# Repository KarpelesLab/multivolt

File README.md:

# MultiVolt — breadboard power & level-translation boards

Two KiCad 10 boards, designed for JLCPCB assembly:

| Board | What it is | Size | Parts cost* |
|---|---|---|---|
| **MultiVolt PSU** (`boards/mvpsu`) | USB-C PD supply that plugs into both breadboard power-rail pairs. Each side gets its own voltage, picked with a jumper: **1.2 / 1.5 / 1.8 / 2.5 / 3.3 / 5.0 V**. Latching overcurrent protection with LEDs. | 60 × 57 mm | ≈ $6.9 |
| **MultiVolt LVL4** (`boards/lvl4`) | 4-channel fixed-direction level translator, DIP-20 footprint (straddles the centre channel). | 12.7 × 30 mm | ≈ $1.35 |

\*Parts only, JLCPCB prices at qty 50/100, October 2026. Extended-part setup fees, PCB and assembly cost come on top.

### Repository layout
```
designs/       board descriptions (Python) - edit these, not the KiCad files
  psu.py         MultiVolt PSU
  iomodule.py    MultiVolt LVL4
lib/           custom KiCad symbol (INA301)
tools/         generator: schematic writer, PCB builder, autoroute, JLC export, BOM checker
boards/<name>/ generated KiCad 10 project (.kicad_sch/.kicad_pcb/.kicad_pro)
  fab/           gerbers zip, JLC BOM + CPL, schematic PDF, 3D renders
```

---

## MultiVolt PSU

### How it works
* **Input:** USB-C. A **CH224A** asks the charger for **9 V** over USB PD. If the charger can't do PD, the board still runs from 5 V, but the 5 V setting then gives about 4.8 V.
* **Two rails (L / R), each a TPS62933P synchronous buck** (3 A part, 500 kHz). Usable output is **up to 2 A per rail**, set by the protection.
* **Voltage select:** a 2×6 header per rail. Each row is one voltage; put a single jumper across the row you want.
  * **No jumper = rail off (≈0 V).** The FB pin is pulled to 3.3 V through 1 MΩ, so the converter just idles.
  * Two jumpers by mistake: the output lands *between* the two choices, never above the higher one.
  * Computed outputs: 1.202 / 1.500 / 1.800 / 2.501 / 3.296 / 4.992 V nominal, within about ±2 % worst case (see `tools/fb_string.py`).
  * Feedback is taken *after* the current shunt, so the shunt's voltage drop doesn't lower the output.
* **Protection:** an **INA301** watches a 50 mΩ shunt on each rail. Over the limit, it latches, pulls the buck's EN low and lights the **red OC LED**.
  * **ILIM jumper fitted = 1 A trip, removed = 2 A.**
  * Press **RESET** to re-arm both rails.
  * A ~94 µs filter stops normal capacitor inrush from tripping it. Short-circuit current is still limited cycle by cycle inside the TPS62933.
* **LEDs:**
  * **PD** (yellow): the PD contract was negotiated.
  * **OK** (yellow-green, one per rail): the converter reports power-good.
  * **OC** (red, one per rail): overcurrent latched.
* **Outputs:** the rail pins plug into both breadboard power-rail pairs (GND, + on each side). There's also a 4-pin **AUX** header (L+, G, G, R+) for wiring off-board.
* A 1 kΩ bleeder on each rail drops the old voltage in about 35 ms after you switch to a lower setting. The buck can't pull its output down by itself.

### Breadboard rail pins
Sized for MB102-style 830-point breadboards, 55–56 mm wide.

* **Positions:** the inner rail holes are 0.825″ (20.955 mm) from the centreline and the outer ones 0.925″ (23.495 mm). The rail pairs are half a pitch off the 0.1″ grid of the main area.
* **Pins:** each side has **two 2-pin headers in holes 1 and 5 of a rail group (10.16 mm apart)**, so the board sits firmly. Rail holes come in groups of five with a blank position between groups.
* **Polarity:** the order is **GND, +** on both sides, reading left to right with the USB connector facing away from the breadboard. To flip it to + then GND, set `RAIL_ORDER = "+G"` in `designs/psu.py` and regenerate.
* **Mounting:** the headers go on the **bottom** side, pins pointing down.

### Usage notes
* Choose the voltage **before** connecting sensitive parts. Changing the jumper on a live, loaded rail can trip OC: press RESET.
* The OK LED stays off with no jumper. That's expected.
* Inrush: about 46 µF across VBUS. PD chargers are fine with this, but it's above the old USB 2.0 limit of 10 µF.

---

## MultiVolt LVL4 (level translator)

Four **SN74LXC1T45** channels. Each side runs from its own supply, **1.1–5.5 V**, up to 420 Mbps. There's **no automatic direction sensing**: each channel's direction is set by its DIR pin.

* **Input threshold** follows the supply of the *input* side. The **output** swings to the supply of the *output* side.
* **DIRn high or unconnected** (100 k pull-up to VA) = **A → B**. **DIRn tied to GND** = **B → A**. DIR is referenced to **VA**.
* Push-pull only. **Not suitable for I²C or other open-drain buses.**

```
          ┌──────── LVL4 ────────┐
   VA   1 │●                     │ 1  VB
   A1   2 │                      │ 2  B1
   DIR1 3 │                      │ 3  GND
   A2   4 │                      │ 4  B2
   DIR2 5 │                      │ 5  GND
   A3   6 │                      │ 6  B3
   DIR3 7 │                      │ 7  GND
   A4   8 │                      │ 8  B4
   DIR4 9 │                      │ 9  GND
   GND 10 │                      │ 10 GND
          └──────────────────────┘   rows 0.3" apart (DIP-20)
```
Typical setup: VA and VB come from the two PSU rails, for example the L rail at 1.8 V and the R rail at 3.3 V.

---

## Ordering at JLCPCB
Upload these files from `boards/<name>/fab/`:
* `<name>_gerbers.zip`
* `<name>_bom_jlc.csv`
* `<name>_cpl_jlc.csv`

Board settings: 2 layers, 1.6 mm, any finish.

* **Check part rotations in JLC's placement preview before paying.** KiCad and LCSC sometimes disagree on which way a package faces. Rotation fixes go in `ROT_FIX` in `tools/jlc_files.py`. Connectors whose KiCad origin isn't the part centre (pin headers, USB-C) are placed on their pad centre (`PAD_CENTER`).
* The pin headers are through-hole parts. Use JLC's THT assembly option or solder them yourself. On both boards the breadboard headers mount on the **bottom** side.
* Jumper shunts aren't in the BOM: 2 to 4 per PSU (one per VSEL header, plus one per ILIM header if you want the 1 A trip). Standard 2.54 mm shunts, e.g. LCSC C100114.
* Rules used: 0.15 mm clearance, 0.10 mm minimum trace (only at fine-pitch pads), 0.3 mm vias. All within JLC's standard 2-layer process.

## Regenerating
Everything is generated from Python. Edit `designs/*.py`, then run:
```sh
tools/make_board.sh designs/psu.py mvpsu --passes 40      # schematic, ERC, netlist check, PCB, autoroute, DRC
tools/make_board.sh designs/iomodule.py lvl4 --passes 25
tools/fab.sh mvpsu && tools/fab.sh lvl4                     # gerbers, BOM, CPL, PDF, renders
python3 tools/check_bom.py boards/mvpsu/mvpsu.design.json 50   # live JLC stock/price check
```
Requires KiCad 10 (macOS paths in the scripts). Run `tools/setup.sh` once to download Freerouting 2.5 and a Java 25 runtime into `tools/bin/` (not committed).

The switching-regulator power paths, VBUS distribution and rail outputs are hand-placed in the design files. Freerouting routes the remaining signals.

## Before a production run
These boards haven't been built yet. On the first prototypes:
1. Check each tap's output voltage with no load and with a 1 A load.
2. Run a load step on the 1.2 V and 5 V taps to check for ringing. This is the TPS62933 loop with 4.7 µH and 3×22 µF across the whole 1.2–5 V range.
3. Confirm the OC trip point and RESET behaviour.
4. Check how hot the converters get at 2 A.

## License
Copyright 2026 Karpeles Lab Inc.

This hardware design, including the generator scripts that produce it, is licensed under the **CERN Open Hardware Licence Version 2 – Strongly Reciprocal** (CERN-OHL-S v2). See [`LICENSE`](LICENSE).

You may build, modify, sell and distribute boards made from this design. If you distribute boards or modified designs, you must keep the copyright and licence notices and make your complete modified source available under the same licence.

Source location: <https://github.com/KarpelesLab/multivolt>

This source is distributed WITHOUT ANY EXPRESS OR IMPLIED WARRANTY, INCLUDING OF MERCHANTABILITY, SATISFACTORY QUALITY AND FITNESS FOR A PARTICULAR PURPOSE. Please see the CERN-OHL-S v2 for applicable conditions.

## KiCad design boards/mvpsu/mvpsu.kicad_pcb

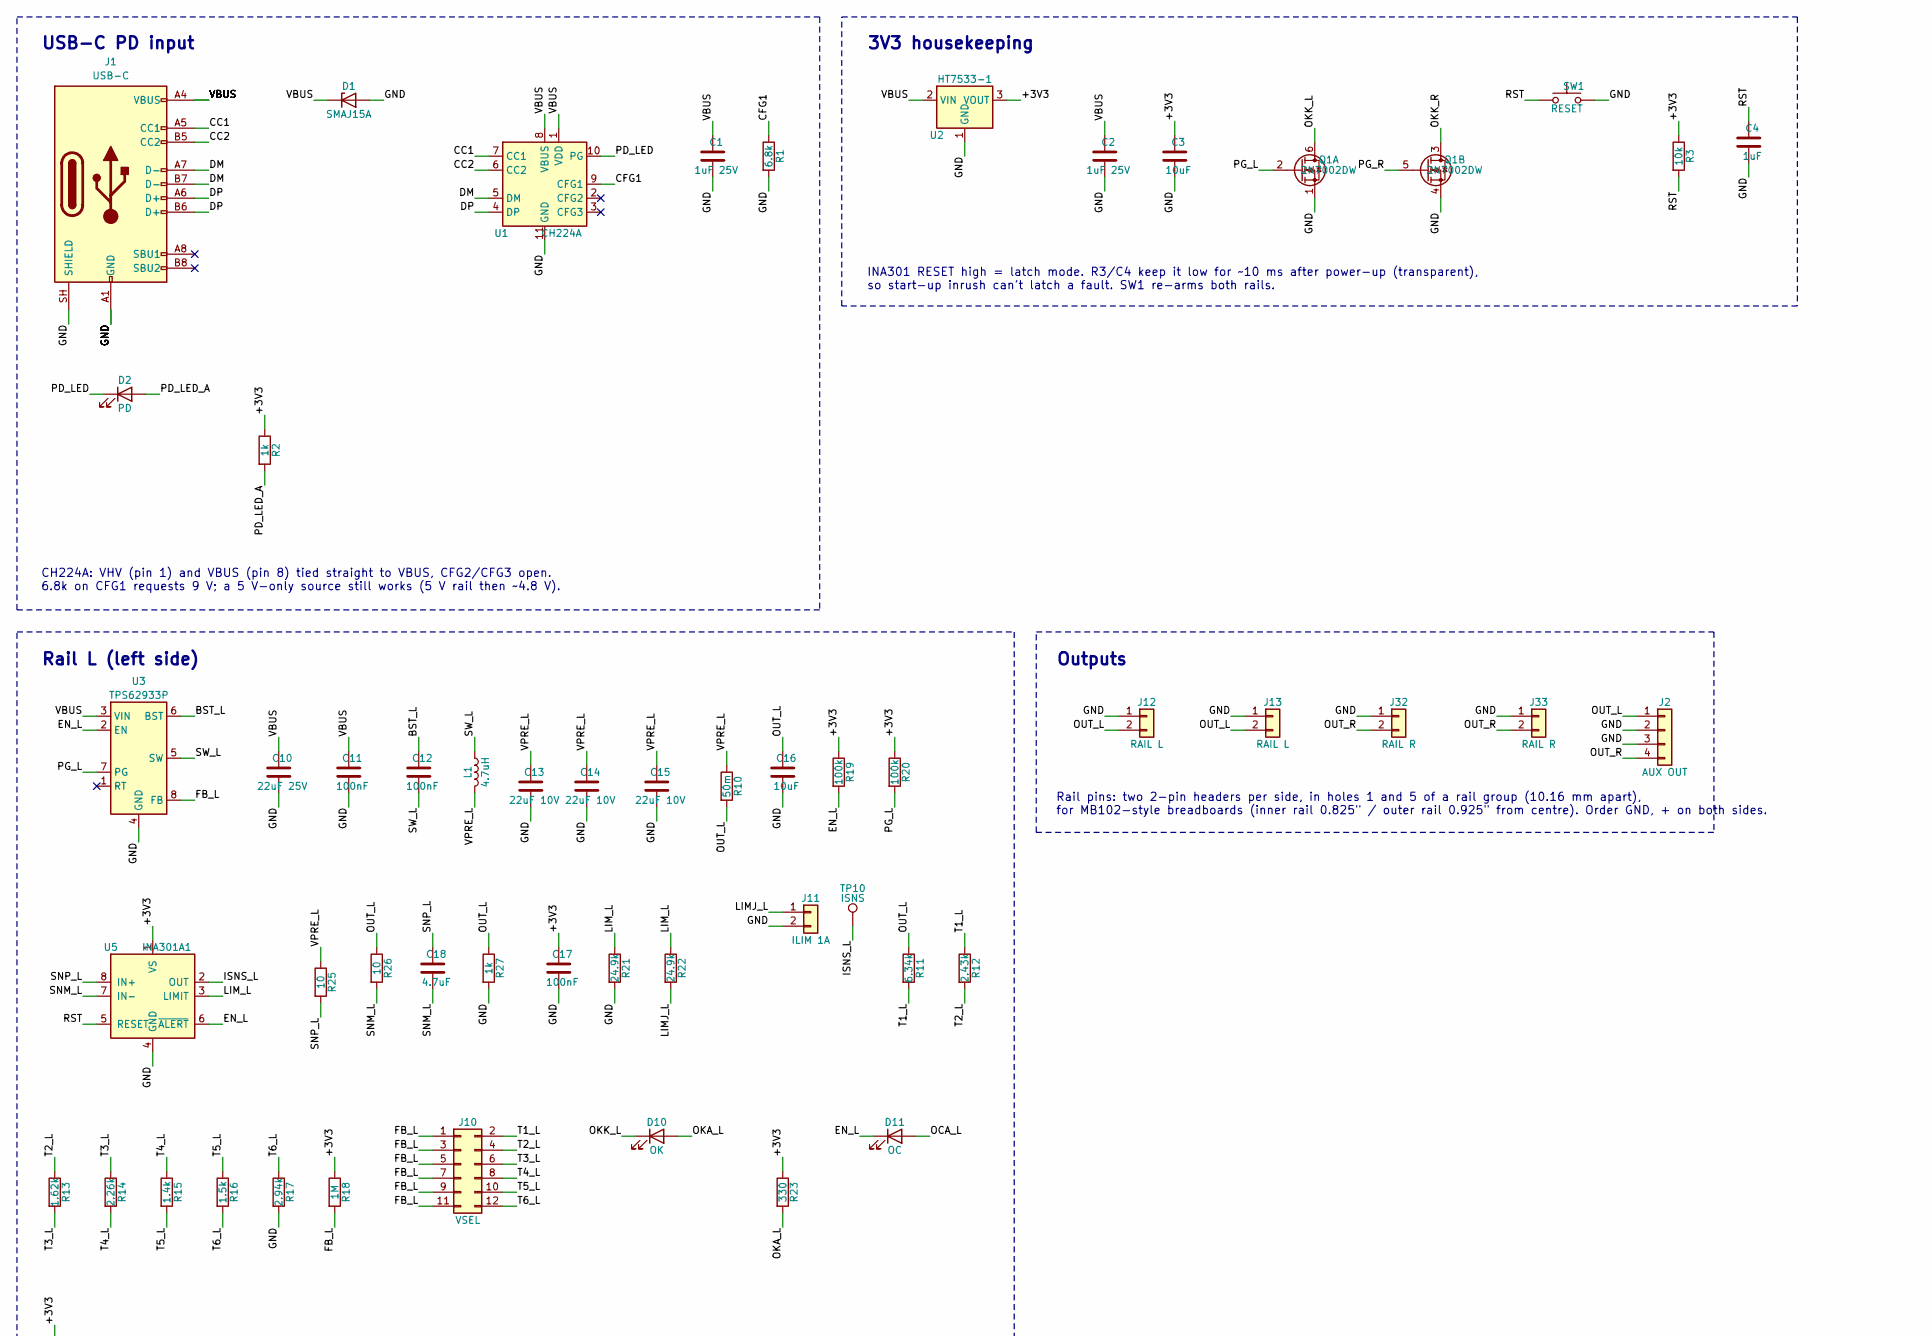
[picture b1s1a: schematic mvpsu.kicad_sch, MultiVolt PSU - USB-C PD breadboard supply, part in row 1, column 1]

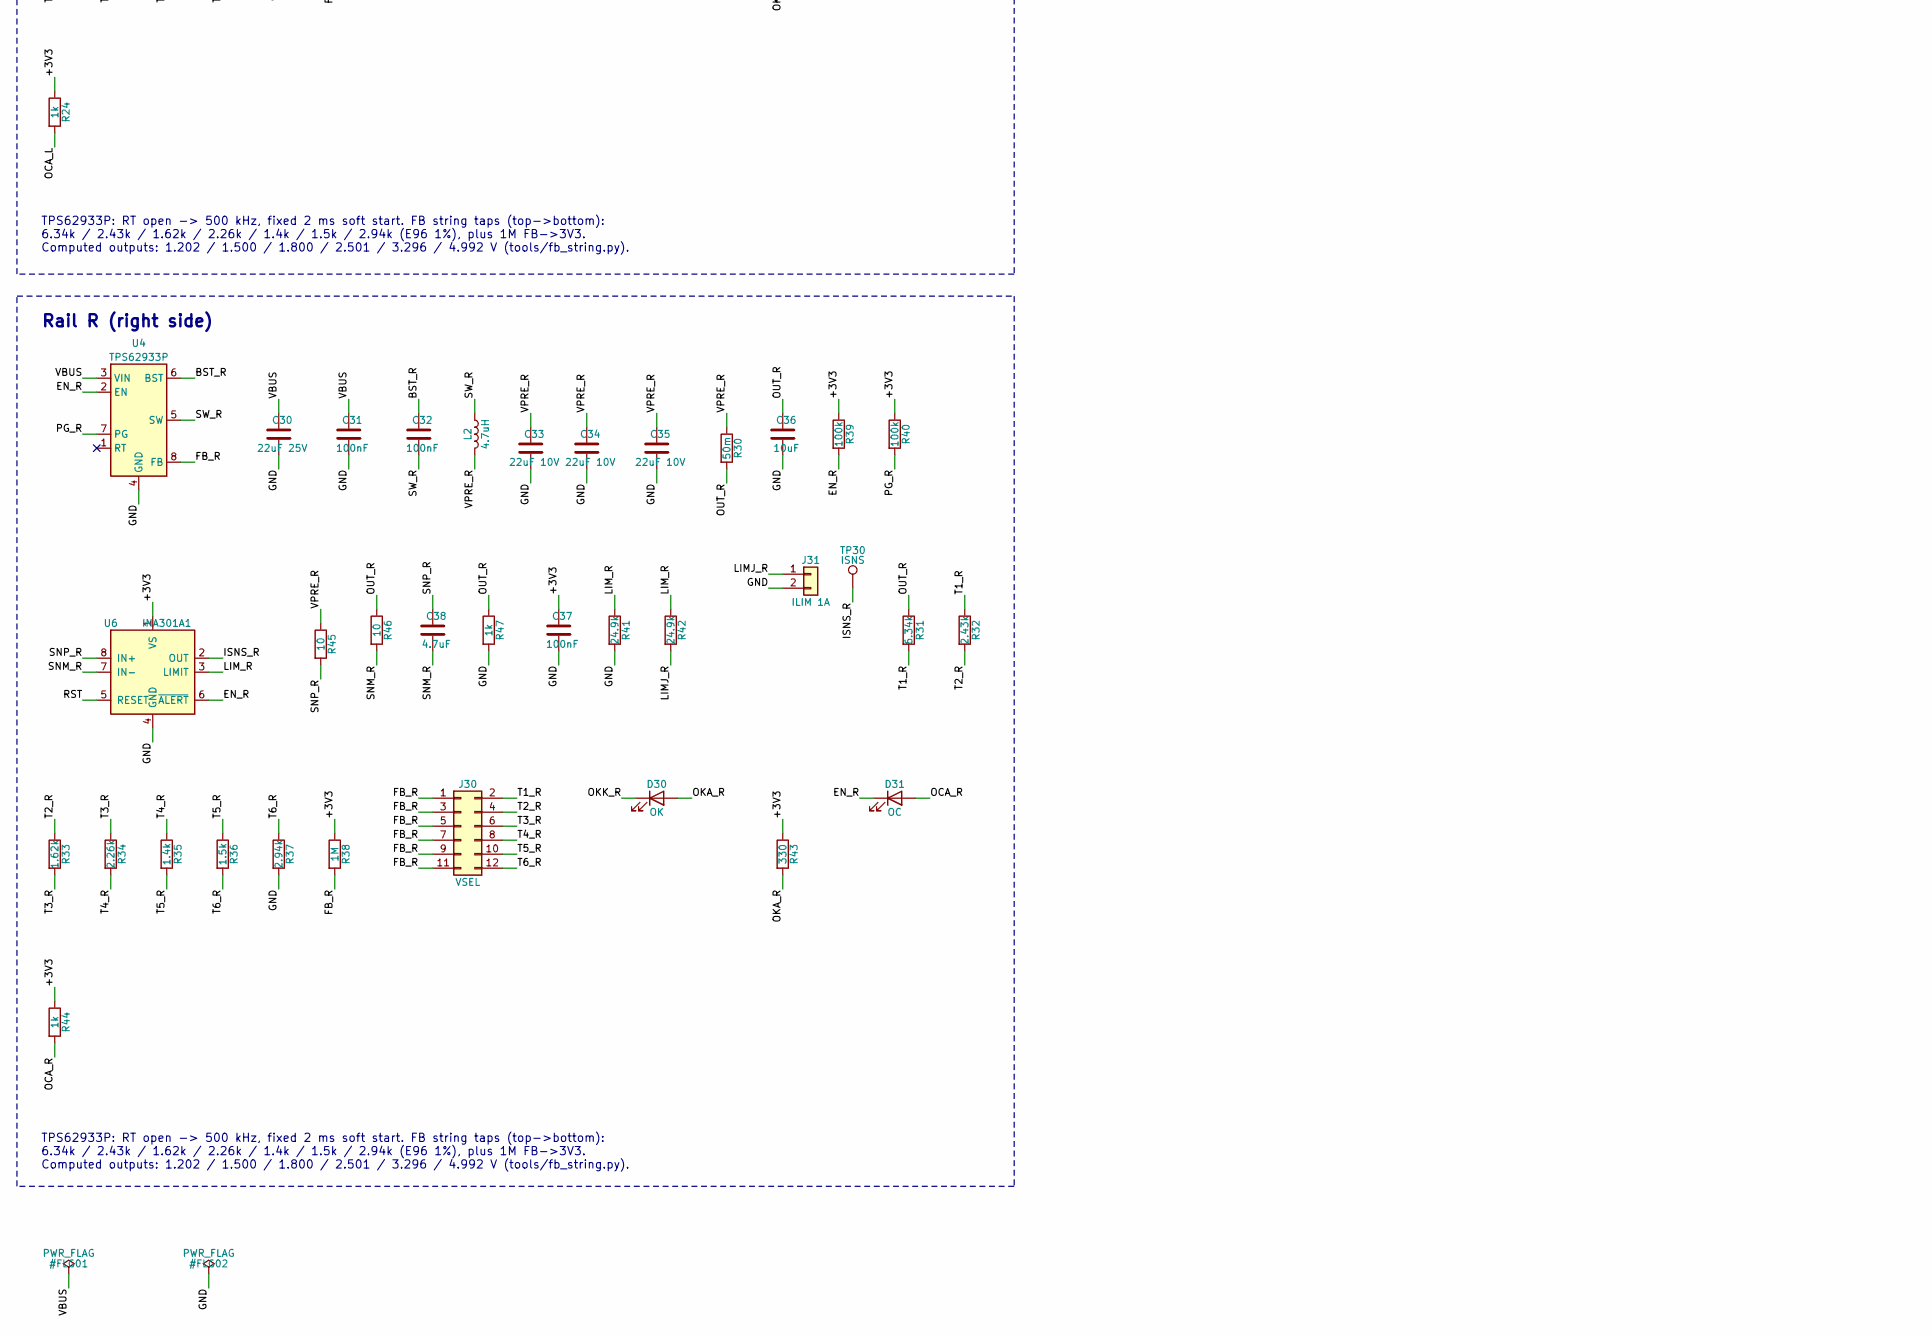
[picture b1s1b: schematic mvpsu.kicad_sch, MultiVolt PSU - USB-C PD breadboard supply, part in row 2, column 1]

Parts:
C1, C2: 1uF 25V; C_0402_1005Metric; LCSC C52923
C3, C16, C36: 10uF; C_0603_1608Metric; LCSC C19702
C4: 1uF; C_0402_1005Metric; LCSC C52923
C10, C30: 22uF 25V; C_1206_3216Metric; LCSC C12891
C11, C12, C17, C31, C32, C37: 100nF; C_0402_1005Metric; LCSC C1525
C13, C14, C15, C33, C34, C35: 22uF 10V; C_0805_2012Metric; LCSC C29277
C18, C38: 4.7uF; C_0402_1005Metric; LCSC C106859
D1: SMAJ15A; D_SMA; LCSC C86819
D2: PD; LED_0603_1608Metric; MPN KT-0603Y; LCSC C2287
D10, D30: OK; LED_0603_1608Metric; MPN KT-0603YG; LCSC C2289
D11, D31: OC; LED_0603_1608Metric; MPN KT-0603R; LCSC C2286
J1: USB-C; USB_C_Receptacle_HRO_TYPE-C-31-M-12; MPN TYPE-C-31-M-12; LCSC C165948
J2: AUX OUT; PinHeader_1x04_P2.54mm_Vertical; LCSC C2691448
J10, J30: VSEL; PinHeader_2x06_P2.54mm_Vertical; LCSC C492423
J11, J31: ILIM 1A; PinHeader_1x02_P2.54mm_Vertical; LCSC C492401
J12, J13: RAIL L; PinHeader_1x02_P2.54mm_Vertical; LCSC C492401
J32, J33: RAIL R; PinHeader_1x02_P2.54mm_Vertical; LCSC C492401
L1, L2: 4.7uH; L_Changjiang_FXL0630; MPN FXL0630-4R7-M; LCSC C167220
Q1: 2N7002DW; SOT-363_SC-70-6; LCSC C61840
R1: 6.8k; R_0402_1005Metric; LCSC C25917
R2, R24, R27, R44, R47: 1k; R_0402_1005Metric; LCSC C11702
R3: 10k; R_0402_1005Metric; LCSC C25744
R10, R30: 50m; R_1206_3216Metric; LCSC C127691
R11, R31: 6.34k; R_0402_1005Metric; LCSC C5713274
R12, R32: 2.43k; R_0402_1005Metric; LCSC C830241
R13, R33: 1.62k; R_0402_1005Metric; LCSC C138038
R14, R34: 2.26k; R_0402_1005Metric; LCSC C226955
R15, R35: 1.4k; R_0402_1005Metric; LCSC C2974008
R16, R36: 1.5k; R_0402_1005Metric; LCSC C25867
R17, R37: 2.94k; R_0402_1005Metric; LCSC C42396634
R18, R38: 1M; R_0402_1005Metric; LCSC C26083
R19, R20, R39, R40: 100k; R_0402_1005Metric; LCSC C25741
R21, R22, R41, R42: 24.9k; R_0402_1005Metric; LCSC C138027
R23, R43: 330; R_0402_1005Metric; LCSC C25104
R25, R26, R45, R46: 10; R_0402_1005Metric; LCSC C25077
SW1: RESET; SW_Push_1P1T_XKB_TS-1187A; LCSC C318884
TP10, TP30: ISNS; TestPoint_Pad_D1.5mm
U1: CH224A; SSOP-10-1EP_3.9x4.9mm_P1mm_EP2.1x3.3mm; MPN CH224A; LCSC C42459160
U2: HT7533-1; SOT-89-3; LCSC C14289
U3, U4: TPS62933P; SOT-583-8; MPN TPS62933PDRLR; LCSC C5219254
U5, U6: INA301A1; VSSOP-8_3x3mm_P0.65mm; MPN INA301A1IDGKR; LCSC C471062

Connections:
+3V3: C3.1, C17.1, C37.1, R2.1, R3.1, R18.1, R19.1, R20.1, R23.1, R24.1, R38.1, R39.1, R40.1, R43.1, R44.1, U2.3 (VOUT), U5.1 (VS), U6.1 (VS)
BST_L: C12.1, U3.6 (BST)
BST_R: C32.1, U4.6 (BST)
CC1: J1.A5 (CC1), U1.7 (CC1)
CC2: J1.B5 (CC2), U1.6 (CC2)
CFG1: R1.1, U1.9 (CFG1)
DM: J1.A7 (D-), J1.B7 (D-), U1.5 (DM)
DP: J1.A6 (D+), J1.B6 (D+), U1.4 (DP)
EN_L: D11.1 (K), R19.2, U3.2 (EN), U5.6 (~ALERT)
EN_R: D31.1 (K), R39.2, U4.2 (EN), U6.6 (~ALERT)
FB_L: J10.1, J10.3, J10.5, J10.7, J10.9, J10.11, R18.2, U3.8 (FB)
FB_R: J30.1, J30.3, J30.5, J30.7, J30.9, J30.11, R38.2, U4.8 (FB)
GND: C1.2, C2.2, C3.2, C4.2, C10.2, C11.2, C13.2, C14.2, C15.2, C16.2, C17.2, C30.2, C31.2, C33.2, C34.2, C35.2, C36.2, C37.2, D1.2 (A), J1.A1 (GND), J1.A12 (GND), J1.B1 (GND), J1.B12 (GND), J1.SH (SHIELD), J2.2, J2.3, J11.2, J12.1, J13.1, J31.2, J32.1, J33.1, Q1.1 (S), Q1.4 (S), R1.2, R17.2, R21.2, R27.2, R37.2, R41.2, R47.2, SW1.2, U1.11 (GND), U2.1 (GND), U3.4 (GND), U4.4 (GND), U5.4 (GND), U6.4 (GND)
ISNS_L: TP10.1, U5.2 (OUT)
ISNS_R: TP30.1, U6.2 (OUT)
LIMJ_L: J11.1, R22.2
LIMJ_R: J31.1, R42.2
LIM_L: R21.1, R22.1, U5.3 (LIMIT)
LIM_R: R41.1, R42.1, U6.3 (LIMIT)
OCA_L: D11.2 (A), R24.2
OCA_R: D31.2 (A), R44.2
OKA_L: D10.2 (A), R23.2
OKA_R: D30.2 (A), R43.2
OKK_L: D10.1 (K), Q1.6 (D)
OKK_R: D30.1 (K), Q1.3 (D)
OUT_L: C16.1, J2.1, J12.2, J13.2, R10.2, R11.1, R26.1, R27.1
OUT_R: C36.1, J2.4, J32.2, J33.2, R30.2, R31.1, R46.1, R47.1
PD_LED: D2.1 (K), U1.10 (PG)
PD_LED_A: D2.2 (A), R2.2
PG_L: Q1.2 (G), R20.2, U3.7 (PG)
PG_R: Q1.5 (G), R40.2, U4.7 (PG)
RST: C4.1, R3.2, SW1.1, U5.5 (RESET), U6.5 (RESET)
SNM_L: C18.2, R26.2, U5.7 (IN-)
SNM_R: C38.2, R46.2, U6.7 (IN-)
SNP_L: C18.1, R25.2, U5.8 (IN+)
SNP_R: C38.1, R45.2, U6.8 (IN+)
SW_L: C12.2, L1.1, U3.5 (SW)
SW_R: C32.2, L2.1, U4.5 (SW)
T1_L: J10.2, R11.2, R12.1
T1_R: J30.2, R31.2, R32.1
T2_L: J10.4, R12.2, R13.1
T2_R: J30.4, R32.2, R33.1
T3_L: J10.6, R13.2, R14.1
T3_R: J30.6, R33.2, R34.1
T4_L: J10.8, R14.2, R15.1
T4_R: J30.8, R34.2, R35.1
T5_L: J10.10, R15.2, R16.1
T5_R: J30.10, R35.2, R36.1
T6_L: J10.12, R16.2, R17.1
T6_R: J30.12, R36.2, R37.1
VBUS: C1.1, C2.1, C10.1, C11.1, C30.1, C31.1, D1.1 (K), J1.A4 (VBUS), J1.A9 (VBUS), J1.B4 (VBUS), J1.B9 (VBUS), U1.1 (VDD), U1.8 (VBUS), U2.2 (VIN), U3.3 (VIN), U4.3 (VIN)
VPRE_L: C13.1, C14.1, C15.1, L1.2, R10.1, R25.1
VPRE_R: C33.1, C34.1, C35.1, L2.2, R30.1, R45.1

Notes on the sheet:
USB-C PD input
CH224A: VHV (pin 1) and VBUS (pin 8) tied straight to VBUS, CFG2/CFG3 open. 6.8k on CFG1 requests 9 V; a 5 V-only source still works (5 V rail then ~4.8 V).
3V3 housekeeping
INA301 RESET high = latch mode. R3/C4 keep it low for ~10 ms after power-up (transparent), so start-up inrush can't latch a fault. SW1 re-arms both rails.
Rail L (left side)
TPS62933P: RT open -> 500 kHz, fixed 2 ms soft start. FB string taps (top->bottom): 6.34k / 2.43k / 1.62k / 2.26k / 1.4k / 1.5k / 2.94k (E96 1%), plus 1M FB->3V3. Computed outputs: 1.202 / 1.500 / 1.800 / 2.501 / 3.296 / 4.992 V (tools/fb_string.py).
Outputs
Rail pins: two 2-pin headers per side, in holes 1 and 5 of a rail group (10.16 mm apart), for MB102-style breadboards (inner rail 0.825" / outer rail 0.925" from centre). Order GND, + on both sides.
Rail R (right side)

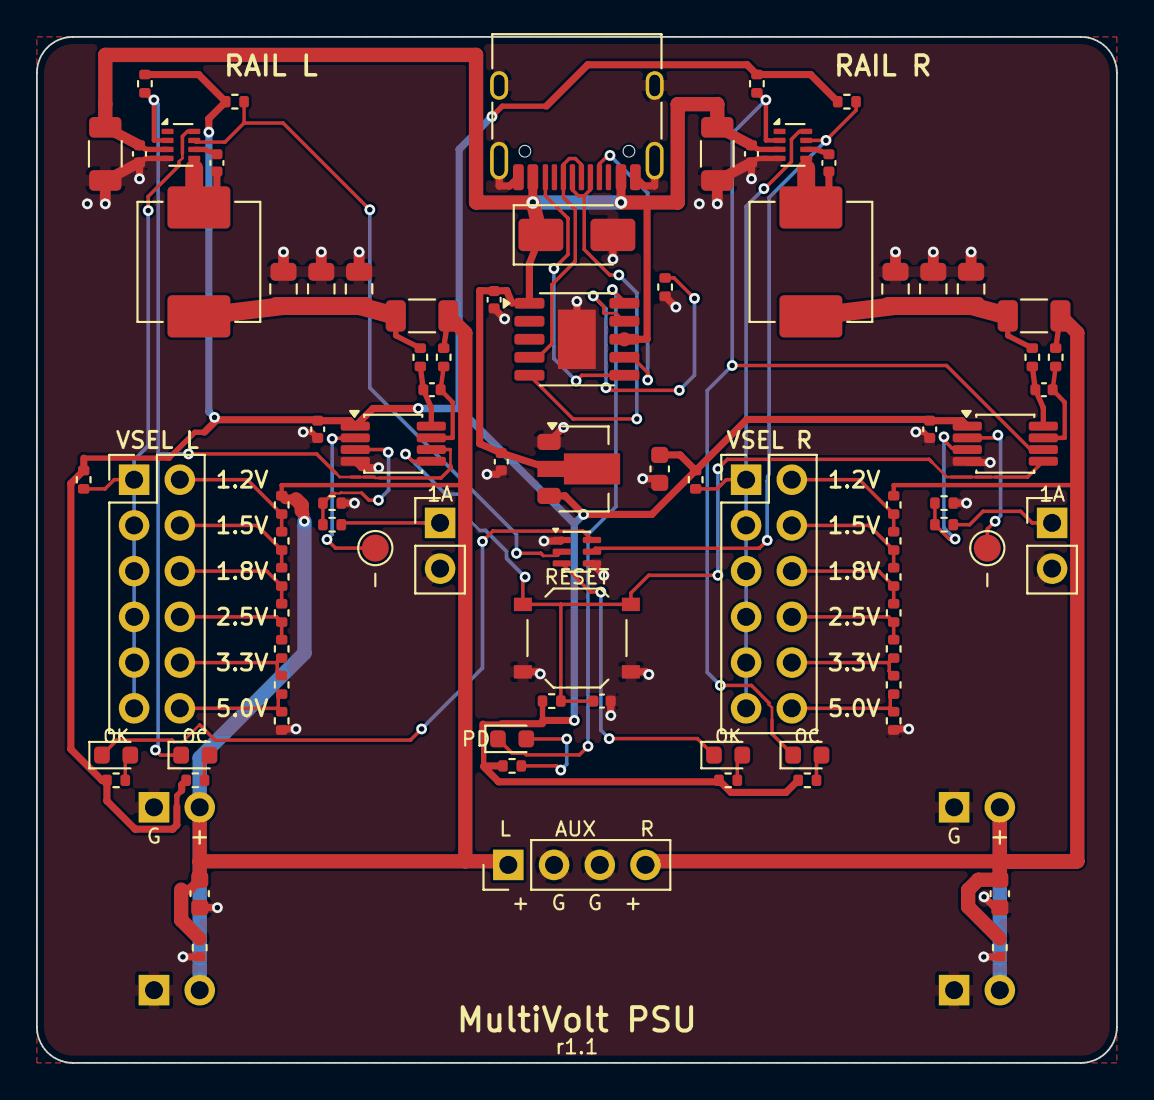
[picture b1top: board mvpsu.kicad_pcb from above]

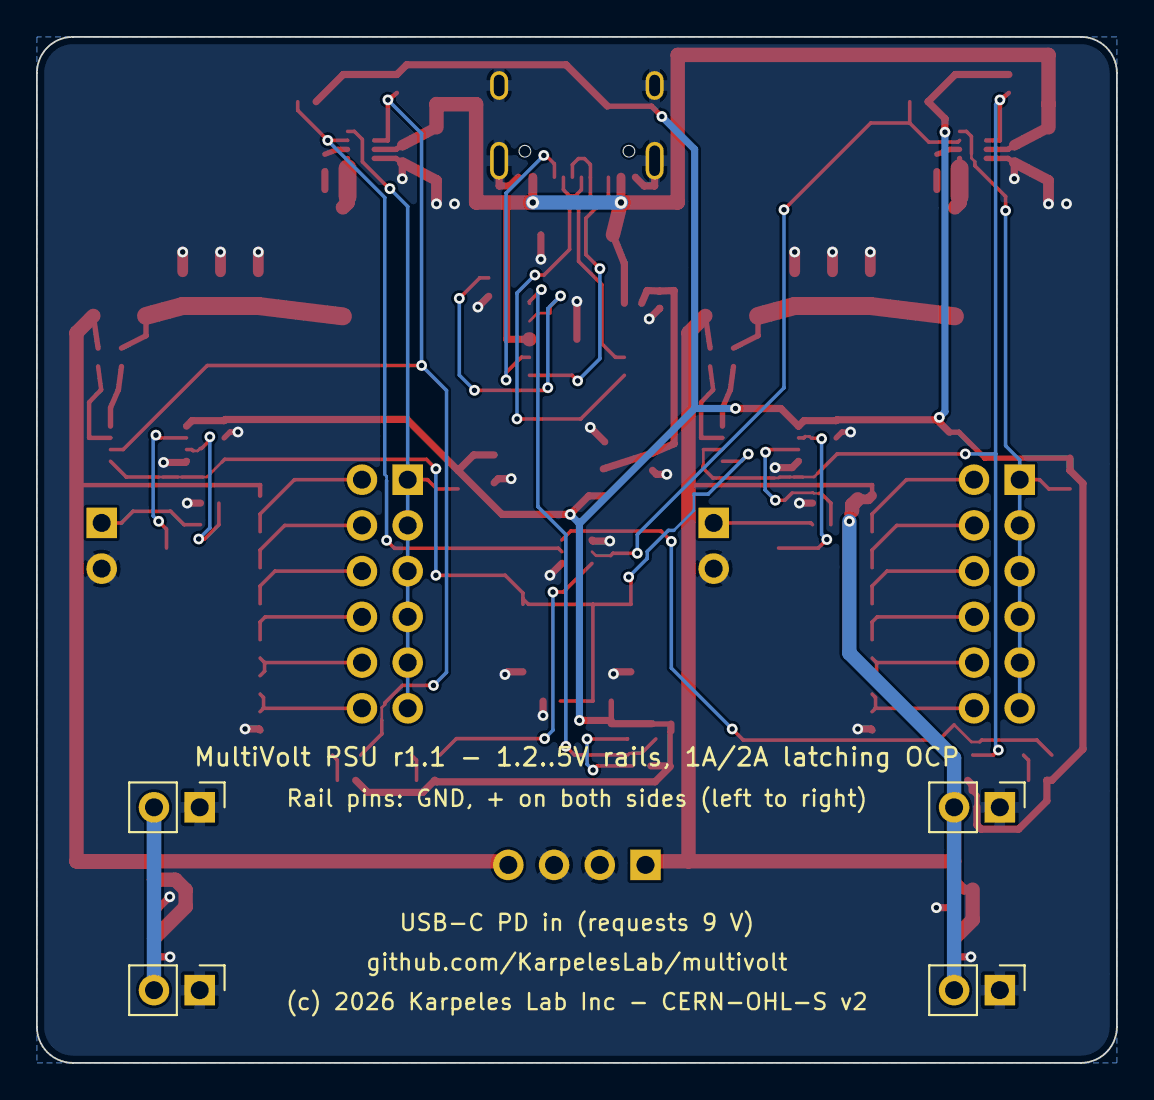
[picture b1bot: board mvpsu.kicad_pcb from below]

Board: 2 copper layers, 60.0 x 57.0 mm, 89 parts (4 on the bottom side), 53 nets.

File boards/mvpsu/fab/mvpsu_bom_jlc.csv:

Comment,Designator,Footprint,LCSC Part #
USB-C,J1,USB_C_Receptacle_HRO_TYPE-C-31-M-12,C165948
SMAJ15A,D1,D_SMA,C86819
CH224A,U1,SSOP-10-1EP_3.9x4.9mm_P1mm_EP2.1x3.3mm,C42459160
1uF 25V,"C1,C2",C_0402_1005Metric,C52923
6.8k,R1,R_0402_1005Metric,C25917
PD,D2,LED_0603_1608Metric,C2287
1k,"R2,R24,R27,R44,R47",R_0402_1005Metric,C11702
HT7533-1,U2,SOT-89-3,C14289
10uF,"C3,C16,C36",C_0603_1608Metric,C19702
2N7002DW,Q1,SOT-363_SC-70-6,C61840
RESET,SW1,SW_Push_1P1T_XKB_TS-1187A,C318884
10k,R3,R_0402_1005Metric,C25744
1uF,C4,C_0402_1005Metric,C52923
TPS62933P,"U3,U4",SOT-583-8,C5219254
22uF 25V,"C10,C30",C_1206_3216Metric,C12891
100nF,"C11,C12,C17,C31,C32,C37",C_0402_1005Metric,C1525
4.7uH,"L1,L2",L_Changjiang_FXL0630,C167220
22uF 10V,"C13,C14,C15,C33,C34,C35",C_0805_2012Metric,C29277
50m,"R10,R30",R_1206_3216Metric,C127691
100k,"R19,R20,R39,R40",R_0402_1005Metric,C25741
INA301A1,"U5,U6",VSSOP-8_3x3mm_P0.65mm,C471062
10,"R25,R26,R45,R46",R_0402_1005Metric,C25077
4.7uF,"C18,C38",C_0402_1005Metric,C106859
24.9k,"R21,R22,R41,R42",R_0402_1005Metric,C138027
ILIM 1A,"J11,J31",PinHeader_1x02_P2.54mm_Vertical,C492401
6.34k,"R11,R31",R_0402_1005Metric,C5713274
2.43k,"R12,R32",R_0402_1005Metric,C830241
1.62k,"R13,R33",R_0402_1005Metric,C138038
2.26k,"R14,R34",R_0402_1005Metric,C226955
1.4k,"R15,R35",R_0402_1005Metric,C2974008
1.5k,"R16,R36",R_0402_1005Metric,C25867
2.94k,"R17,R37",R_0402_1005Metric,C42396634
1M,"R18,R38",R_0402_1005Metric,C26083
VSEL,"J10,J30",PinHeader_2x06_P2.54mm_Vertical,C492423
OK,"D10,D30",LED_0603_1608Metric,C2289
330,"R23,R43",R_0402_1005Metric,C25104
OC,"D11,D31",LED_0603_1608Metric,C2286
RAIL L,"J12,J13",PinHeader_1x02_P2.54mm_Vertical,C492401
RAIL R,"J32,J33",PinHeader_1x02_P2.54mm_Vertical,C492401
AUX OUT,J2,PinHeader_1x04_P2.54mm_Vertical,C2691448

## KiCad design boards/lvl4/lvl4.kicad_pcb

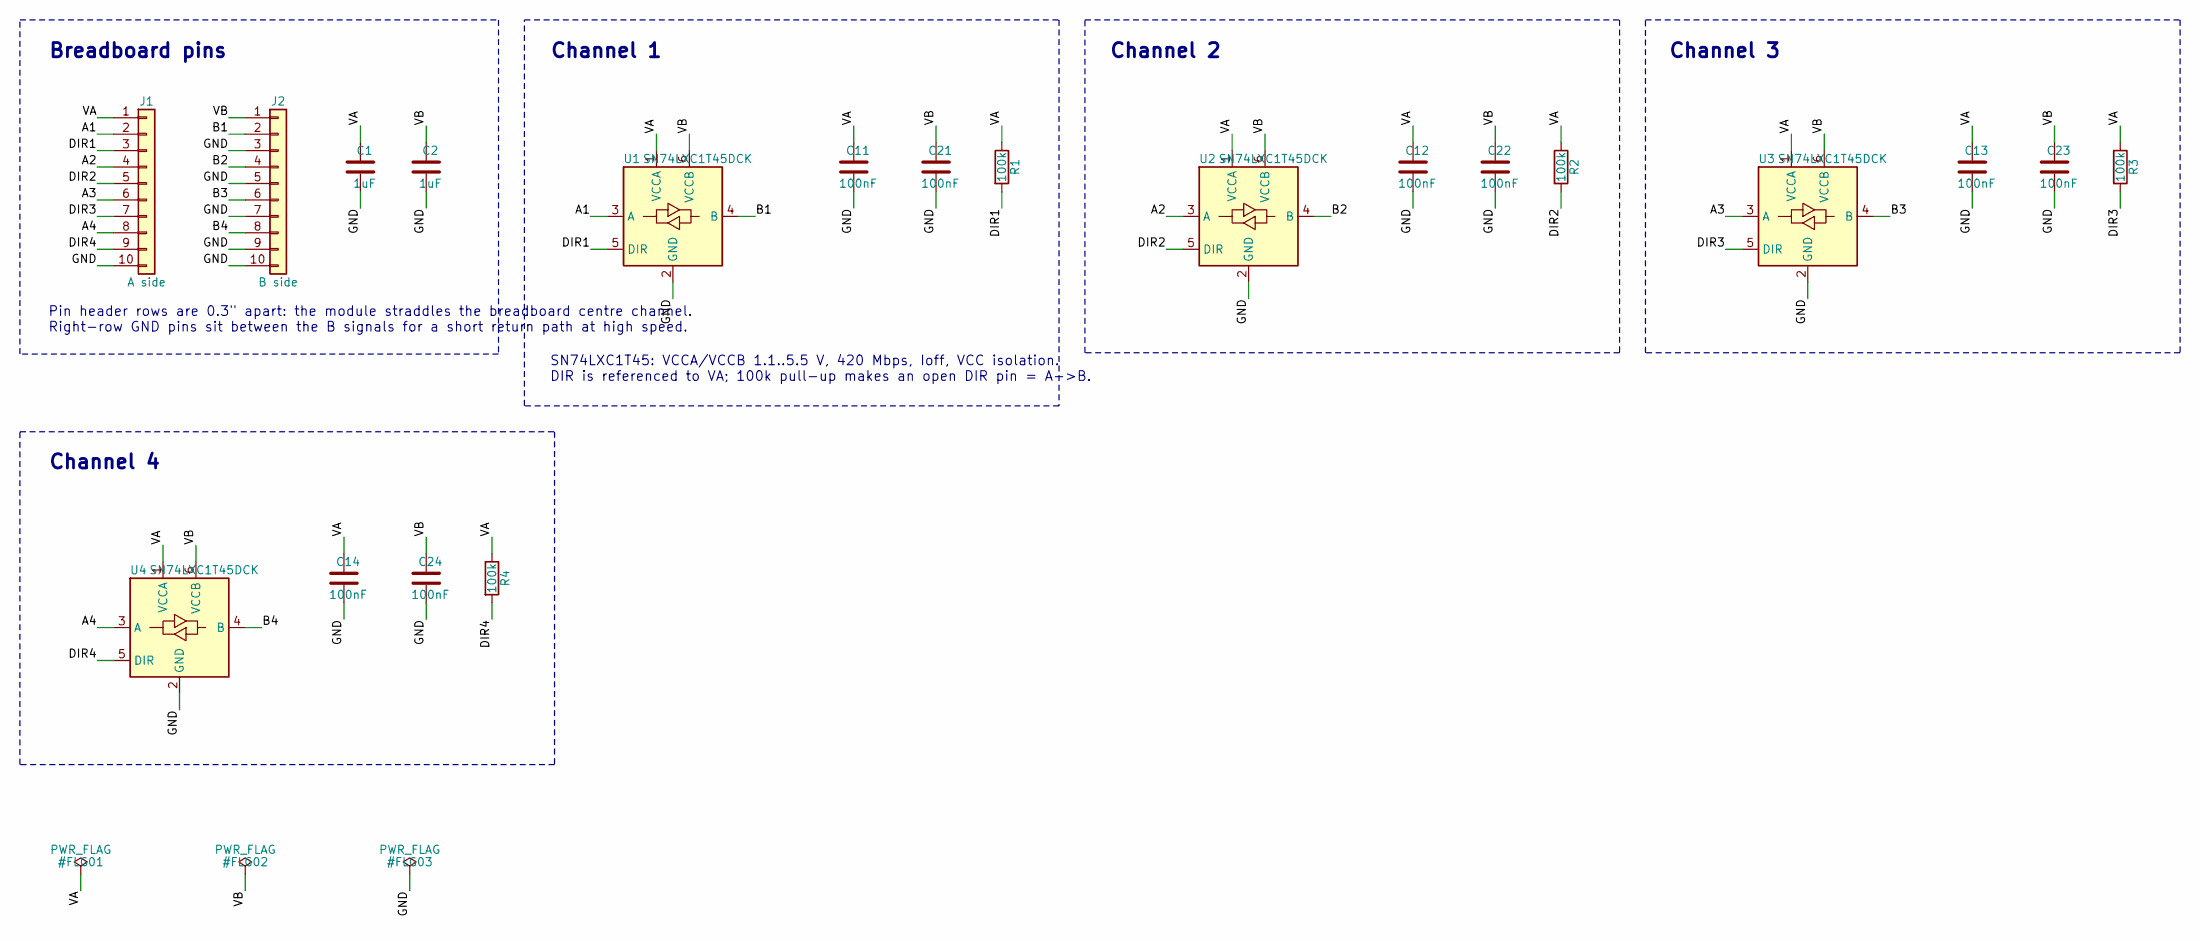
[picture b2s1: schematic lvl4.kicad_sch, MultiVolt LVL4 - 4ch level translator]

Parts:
C1, C2: 1uF; C_0402_1005Metric; LCSC C52923
C11, C12, C13, C14, C21, C22, C23, C24: 100nF; C_0402_1005Metric; LCSC C1525
J1: A side; PinHeader_1x10_P2.54mm_Vertical; LCSC C492409
J2: B side; PinHeader_1x10_P2.54mm_Vertical; LCSC C492409
R1, R2, R3, R4: 100k; R_0402_1005Metric; LCSC C25741
U1, U2, U3, U4: SN74LXC1T45DCK; SOT-363_SC-70-6; MPN SN74LXC1T45DCKR; LCSC C5217888

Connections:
A1: J1.2, U1.3 (A)
A2: J1.4, U2.3 (A)
A3: J1.6, U3.3 (A)
A4: J1.8, U4.3 (A)
B1: J2.2, U1.4 (B)
B2: J2.4, U2.4 (B)
B3: J2.6, U3.4 (B)
B4: J2.8, U4.4 (B)
DIR1: J1.3, R1.2, U1.5 (DIR)
DIR2: J1.5, R2.2, U2.5 (DIR)
DIR3: J1.7, R3.2, U3.5 (DIR)
DIR4: J1.9, R4.2, U4.5 (DIR)
GND: C1.2, C2.2, C11.2, C12.2, C13.2, C14.2, C21.2, C22.2, C23.2, C24.2, J1.10, J2.3, J2.5, J2.7, J2.9, J2.10, U1.2 (GND), U2.2 (GND), U3.2 (GND), U4.2 (GND)
VA: C1.1, C11.1, C12.1, C13.1, C14.1, J1.1, R1.1, R2.1, R3.1, R4.1, U1.1 (VCCA), U2.1 (VCCA), U3.1 (VCCA), U4.1 (VCCA)
VB: C2.1, C21.1, C22.1, C23.1, C24.1, J2.1, U1.6 (VCCB), U2.6 (VCCB), U3.6 (VCCB), U4.6 (VCCB)

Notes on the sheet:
Breadboard pins
Pin header rows are 0.3" apart: the module straddles the breadboard centre channel. Right-row GND pins sit between the B signals for a short return path at high speed.
Channel 1
SN74LXC1T45: VCCA/VCCB 1.1..5.5 V, 420 Mbps, Ioff, VCC isolation. DIR is referenced to VA; 100k pull-up makes an open DIR pin = A->B.
Channel 2
Channel 3
Channel 4

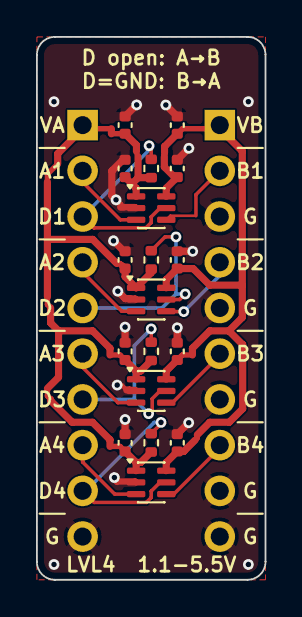
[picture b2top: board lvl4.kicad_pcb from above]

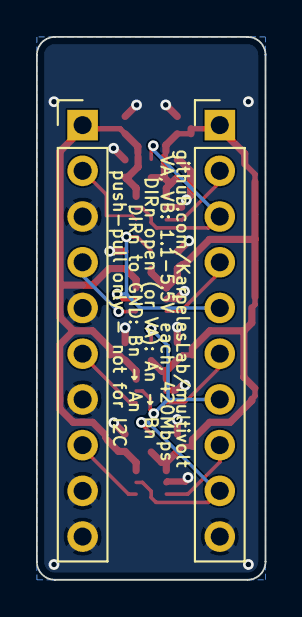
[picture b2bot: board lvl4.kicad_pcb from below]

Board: 2 copper layers, 12.7 x 30.2 mm, 20 parts (2 on the bottom side), 15 nets.

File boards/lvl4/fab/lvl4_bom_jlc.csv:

Comment,Designator,Footprint,LCSC Part #
A side,J1,PinHeader_1x10_P2.54mm_Vertical,C492409
B side,J2,PinHeader_1x10_P2.54mm_Vertical,C492409
1uF,"C1,C2",C_0402_1005Metric,C52923
SN74LXC1T45DCK,"U1,U2,U3,U4",SOT-363_SC-70-6,C5217888
100nF,"C11,C12,C13,C14,C21,C22,C23,C24",C_0402_1005Metric,C1525
100k,"R1,R2,R3,R4",R_0402_1005Metric,C25741

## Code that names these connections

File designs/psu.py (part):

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    d.add("D1", "Device:D_Zener", "SMAJ15A", "Diode_SMD:D_SMA", pins={"1": "VBUS", "2": "GND"},
          lcsc="C86819", desc="15 V TVS on VBUS", group=g, pcb=dict(x=0, y=11.0, rot=0))
    d.add("U1", "Interface_USB:CH224K", "CH224A", "Package_SO:SSOP-10-1EP_3.9x4.9mm_P1mm_EP2.1x3.3mm",
          pins={"VDD": "VBUS", "VBUS": "VBUS", "CFG1": "CFG1", "CFG2": None, "CFG3": None, "DP": "DP",
                "DM": "DM", "CC1": "CC1", "CC2": "CC2", "PG": "PD_LED", "GND": "GND"},
          lcsc="C42459160", mpn="CH224A", group=g, desc="USB PD sink (pin 1 = VHV on CH224A, 32 V tolerant)",
          pcb=dict(x=0, y=16.8, rot=0))
    d.add("C1", "Device:C", "1uF 25V", C0402, pins={"1": "VBUS", "2": "GND"}, lcsc="C52923", group=g,
          pcb=dict(x=-4.6, y=14.6, rot=270))
    d.add("R1", "Device:R", "6.8k", R0402, pins={"1": "CFG1", "2": "GND"}, lcsc="C25917", group=g,
          desc="CFG1: 6.8k = request 9 V", pcb=dict(x=4.9, y=13.9, rot=270))
    d.add("D2", "Device:LED", "PD", LED0603, pins={"K": "PD_LED", "A": "PD_LED_A"}, lcsc="C2287",
          mpn="KT-0603Y", group=g, pcb=dict(x=-3.6, y=39.0, rot=0))
    d.add("R2", "Device:R", "1k", R0402, pins={"1": "+3V3", "2": "PD_LED_A"}, lcsc="C11702", group=g,
          pcb=dict(x=-3.6, y=40.5, rot=0))
    d.note(g, "CH224A: VHV (pin 1) and VBUS (pin 8) tied straight to VBUS, CFG2/CFG3 open.\n"
              "6.8k on CFG1 requests 9 V; a 5 V-only source still works (5 V rail then ~4.8 V).")
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    d.add("C3", "Device:C", "10uF", C0603, pins={"1": "+3V3", "2": "GND"}, lcsc="C19702", group=g,
          pcb=dict(x=4.6, y=24.0, rot=270))
    d.add("Q1", "Transistor_FET:Q_Dual_NMOS_S1G1D2S2G2D1", "2N7002DW", "Package_TO_SOT_SMD:SOT-363_SC-70-6",
          pins={"1": "GND", "2": "PG_L", "6": "OKK_L", "4": "GND", "5": "PG_R", "3": "OKK_R"},
          lcsc="C61840", group=g, desc="OK LED drivers (power-good is active high)", pcb=dict(x=0, y=28.6, rot=0))
    d.add("SW1", "Switch:SW_Push", "RESET", "Button_Switch_SMD:SW_Push_1P1T_XKB_TS-1187A",
          pins={"1": "RST", "2": "GND"}, lcsc="C318884", group=g, pcb=dict(x=0, y=33.4, rot=0))
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
    # aux output header
    d.add("J2", "Connector_Generic:Conn_01x04", "AUX OUT", HDR + "PinHeader_1x04_P2.54mm_Vertical",
          pins={"1": "OUT_L", "2": "GND", "3": "GND", "4": "OUT_R"}, lcsc="C2691448", group="Outputs",
          desc="rail outputs for wiring off-board (pins up)", pcb=dict(x=-3.81, y=46.0, rot=90))
    d.note("Outputs", "Rail pins: two 2-pin headers per side, in holes 1 and 5 of a rail group (10.16 mm apart),\n"
                      "for MB102-style breadboards (inner rail 0.825\" / outer rail 0.925\" from centre). Order GND, + on both sides.")
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

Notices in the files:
boards/mvpsu/mvpsu.kicad_pcb:
(c) 2026 Karpeles Lab Inc - CERN-OHL-S v2
